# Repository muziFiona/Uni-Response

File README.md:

## Uni-Response
Here is the GitHub page for my course response

There are 2 folders here and will direct you to my works for different unit

For response dealing with physical circuit, arduino, etc. Please go to Advanced-Physical-Computing

https://github.com/muziFiona/Uni-Response/tree/master/Advanced-Physical-Computing

### Advanced-Physical-Computing Response
[Week 1 Practice- The memory Game](https://github.com/muziFiona/Uni-Response/blob/master/Advanced-Physical-Computing/Week_1/Week_01_Mon_response.md "Week 1 link")

[Week 2 Practice- Leds in Serial and Parallel](https://github.com/muziFiona/Uni-Response/blob/master/Advanced-Physical-Computing/Week_2/Week_2_practice.md "Week 2 link")

[Week 3 Practice- Soldering](https://github.com/muziFiona/Uni-Response/blob/master/Advanced-Physical-Computing/Week_3/Week3_practice.md "Week 3 link")

[Week 4 Practice- servo, motor, MPR121 and capacitor](https://github.com/muziFiona/Uni-Response/blob/master/Advanced-Physical-Computing/Week_4/Week_4_practice.md "Week 4 link")

[Week 5 Practice- Project Development](https://github.com/muziFiona/Uni-Response/blob/master/Advanced-Physical-Computing/Week_5/Week_5_practice.md "Week 5 link")

[Week 6 Practice- capacitors + oscillator](https://github.com/muziFiona/Uni-Response/blob/master/Advanced-Physical-Computing/Week_6/Week_6_practice.md "Week 6 link")

[Week 7 Practice- Shift Reg](https://github.com/muziFiona/Uni-Response/blob/master/Advanced-Physical-Computing/Week_7/Week_7_practice.md "Week 7 link")

[Week 8 Practice- Photon Wifi](https://github.com/muziFiona/Uni-Response/blob/master/Advanced-Physical-Computing/Week_8/Week_8_Practice.md "Week 8 link")

[Week 9 Practice-Eagle](https://github.com/muziFiona/Uni-Response/blob/master/Advanced-Physical-Computing/Week_9/Week_9_Practice.md "Week 9 link")

[Project LOG](https://github.com/muziFiona/Uni-Response/blob/master/Advanced-Physical-Computing/Final_Project/LOG_BOOK.md "Project LOG week 5,6,7,8,9")

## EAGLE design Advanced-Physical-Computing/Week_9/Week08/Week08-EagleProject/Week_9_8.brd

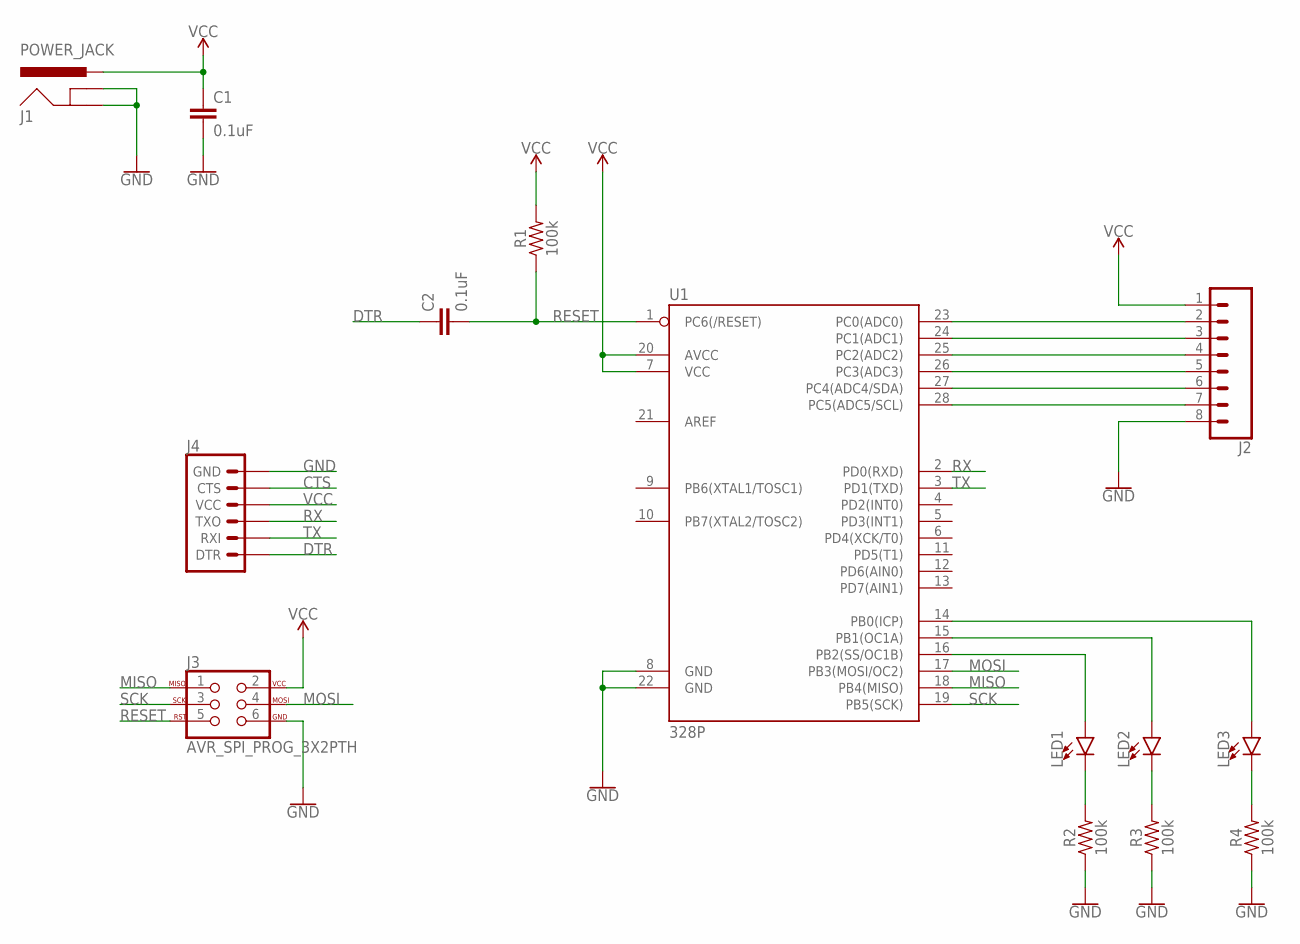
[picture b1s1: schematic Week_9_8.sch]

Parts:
C1, C2: 0.1uF; CAP-PTH-SMALL-KIT
J1: POWER_JACK; POWER_JACK_PTH
J2: CONN_08"; 1X08
J3: AVR_SPI_PROG_3X2PTH; 2X3
J4: 6_PIN_SERIAL_TARGET; 1X06
LED1, LED2, LED3: LED5MM; LED_5MM
R1, R2, R3, R4: 100k; AXIAL-0.3
U1: 328P; DIP28

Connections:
CTS: J4.5 (CTS)
DTR: C2.1, J4.1 (DTR)
GND: C1.2, J1.GND, J1.GNDBREAK, J2.8, J3.6, J4.6 (GND), R2.P$1 (1), R3.P$1 (1), R4.P$1 (1), U1.8 (GND), U1.22 (GND)
MISO: J3.1, U1.18 (PB4(MISO))
MOSI: J3.4, U1.17 (PB3(MOSI/OC2))
unnamed: LED3.K (C), R4.P$2 (2)
unnamed: LED2.K (C), R3.P$2 (2)
unnamed: LED1.K (C), R2.P$2 (2)
unnamed: LED3.A, U1.14 (PB0(ICP))
unnamed: LED2.A, U1.15 (PB1(OC1A))
unnamed: LED1.A, U1.16 (PB2(SS/OC1B))
unnamed: J2.2, U1.23 (PC0(ADC0))
unnamed: J2.3, U1.24 (PC1(ADC1))
unnamed: J2.4, U1.25 (PC2(ADC2))
unnamed: J2.5, U1.26 (PC3(ADC3))
unnamed: J2.6, U1.27 (PC4(ADC4/SDA))
unnamed: J2.7, U1.28 (PC5(ADC5/SCL))
RESET: C2.2, J3.5, R1.P$1 (1), U1.1 (PC6(/RESET))
RX: J4.3 (TXO), U1.2 (PD0(RXD))
SCK: J3.3, U1.19 (PB5(SCK))
TX: J4.2 (RXI), U1.3 (PD1(TXD))
VCC: C1.1, J1.PWR, J2.1, J3.2, J4.4 (VCC), R1.P$2 (2), U1.7 (VCC), U1.20 (AVCC)

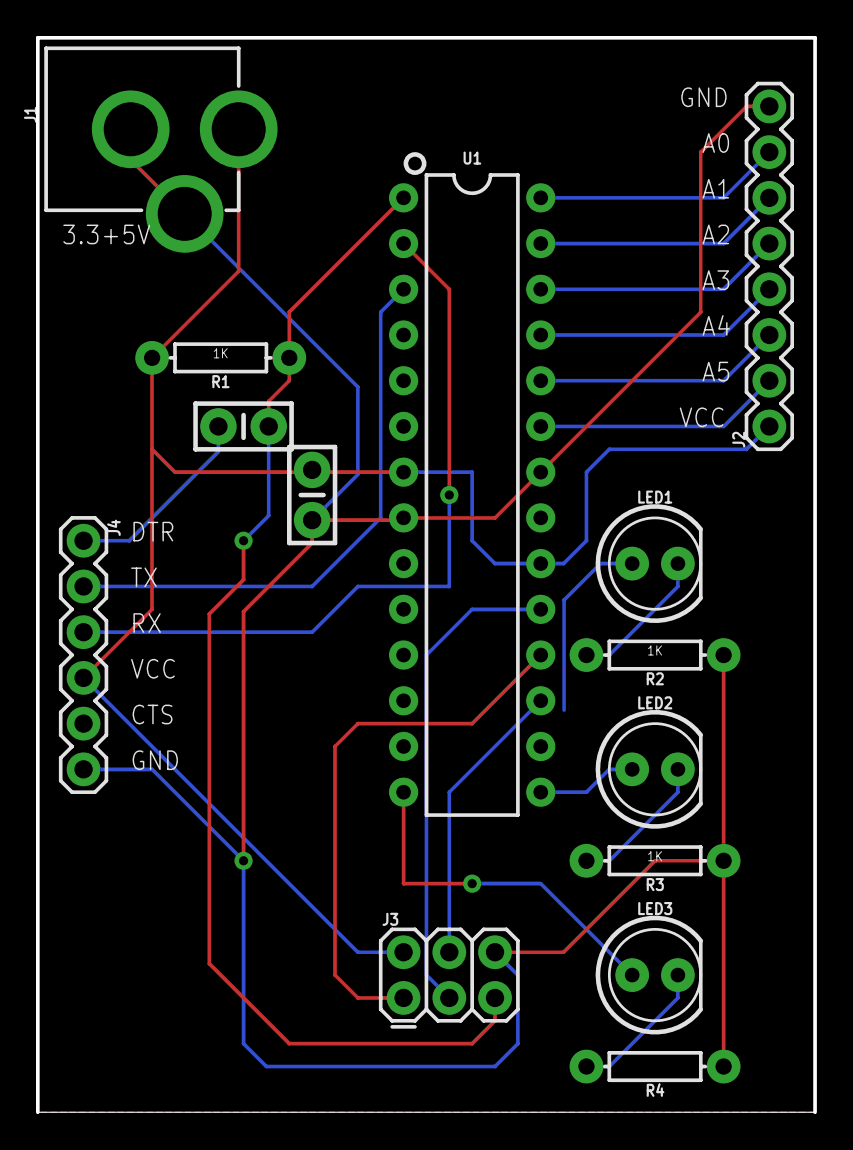
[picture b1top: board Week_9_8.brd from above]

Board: 2 copper layers, 43.2 x 59.7 mm, 14 parts (0 on the bottom side), 21 nets.

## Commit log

2019-10-07 Rename README.md to Week_01_Mon_response
2019-10-07 Rename Week_01_Mon_response to Week_01_Mon_response.md
2019-11-04 Rename README to Testing
2019-11-04 Rename LOG_BOOK.md to README.md
2020-01-31 Create Advanced-Creative-Coding-2
2020-01-31 Rename Advanced-Creative-Coding-2 to Advanced-Creative-Coding-2.md

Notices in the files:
parts and their libraries:
SparkFun-Capacitors: Licensing: Creative Commons ShareAlike 4.0 International - https://creativecommons.org/licenses/by-sa/4.0
